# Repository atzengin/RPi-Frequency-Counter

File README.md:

# 2/4 channel frequency counter for RPi

Provides 2 32 bits or 4 16 bits independent counters on board.
For the UI software see [this page](https://github.com/atzengin/RPi-Frequency-Counter-Software)

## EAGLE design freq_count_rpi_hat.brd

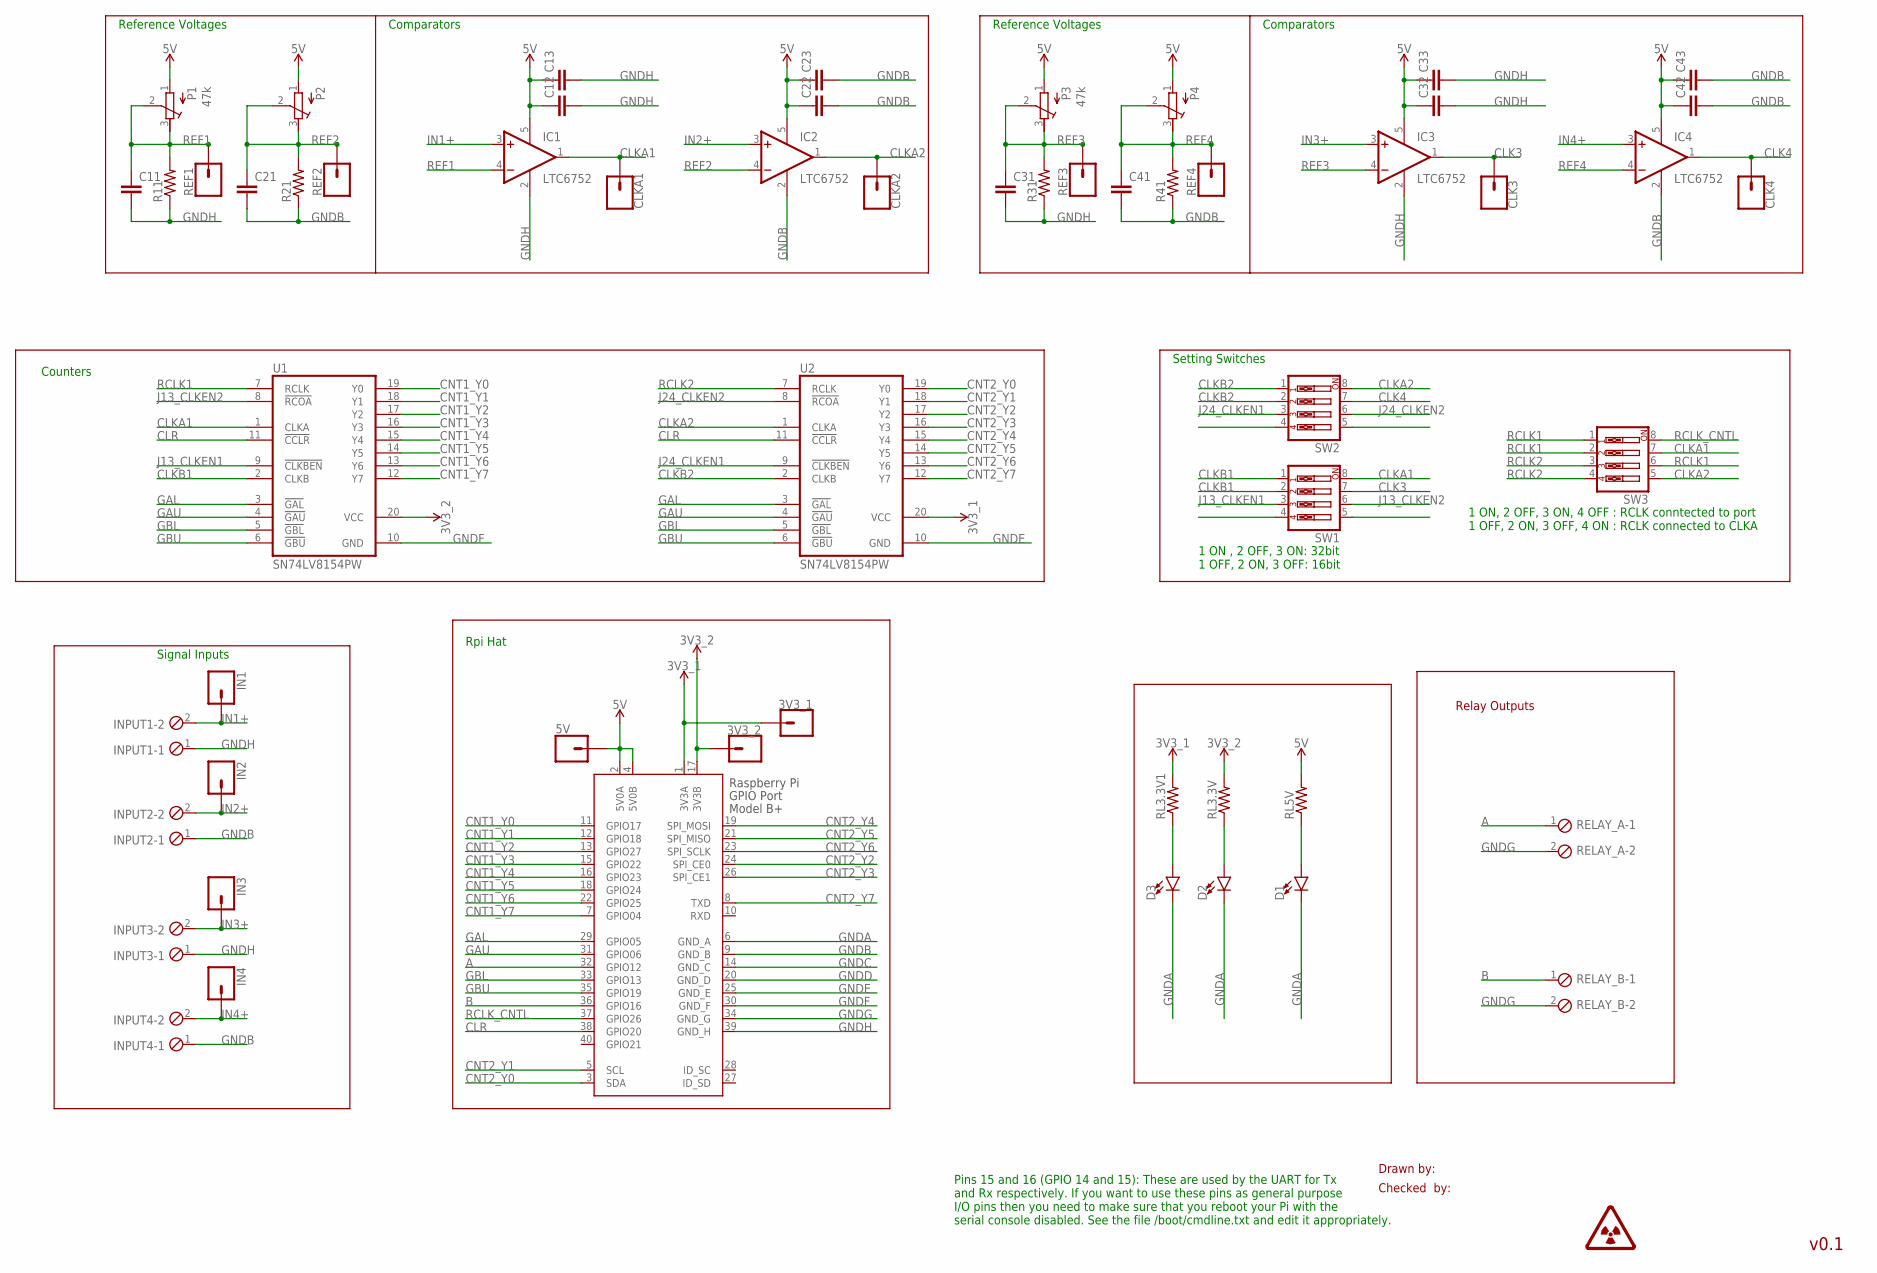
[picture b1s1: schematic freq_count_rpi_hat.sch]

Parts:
3V3_1, 3V3_2, 5V: CONN_01; 1X01
C11, C12, C13, C21, C22, C23, C31, C32, C33, C41, C42, C43: C-EUC1206; C1206
CLK3, CLK4: CONN_01; 1X01
CLKA1, CLKA2: CONN_01; 1X01
D1, D2, D3: LED1206; LED-1206
IC1, IC2, IC3, IC4: LTC6752; SOT23-5
IN1, IN2, IN3, IN4: CONN_01; 1X01
INPUT1, INPUT2, INPUT3, INPUT4: MPT2; 2POL254
P1, P3: 47k; RTRIM3296W
P2, P4: R-TRIMM3296W; RTRIM3296W
R11, R21, R31, R41: R-US_R1206; R1206
REF1, REF2, REF3, REF4: CONN_01; 1X01
RELAY_A: MPT2; 2POL254
RELAY_B: MPT2; 2POL254
RL3.3V, RL3.3V1, RL5V: R-US_R1206; R1206
SW1, SW2, SW3: SW_DIP-4; EDG-04
U1, U2: SN74LV8154PW; TSSOP20
X1: RASPI_BOARD_B+#_H; RASPI_BOARD_B+HAT

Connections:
5V: 5V.1, C12.1, C13.1, C22.1, C23.1, C32.1, C33.1, C42.1, C43.1, IC1.5 (V+), IC2.5 (V+), IC3.5 (V+), IC4.5 (V+), P1.1 (A), P2.1 (A), P3.1 (A), P4.1 (A), RL5V.2, X1.2 (5V0A), X1.4 (5V0B)
A: RELAY_A.1, X1.32 (GPIO12)
B: RELAY_B.1, X1.36 (GPIO16)
CLK3: CLK3.1, IC3.1 (OUT), SW1.7
CLK4: CLK4.1, IC4.1 (OUT), SW2.7
CLKA1: CLKA1.1, IC1.1 (OUT), SW1.8, SW3.7, U1.1 (CLKA)
CLKA2: CLKA2.1, IC2.1 (OUT), SW2.8, SW3.5, U2.1 (CLKA)
CLKB1: SW1.1, SW1.2, U1.2 (CLKB)
CLKB2: SW2.1, SW2.2, U2.2 (CLKB)
CLR: U1.11 (!CCLR!), U2.11 (!CCLR!), X1.38 (GPIO20)
CNT1_Y0: U1.19 (Y0), X1.11 (GPIO17)
CNT1_Y1: U1.18 (Y1), X1.12 (GPIO18)
CNT1_Y2: U1.17 (Y2), X1.13 (GPIO27)
CNT1_Y3: U1.16 (Y3), X1.15 (GPIO22)
CNT1_Y4: U1.15 (Y4), X1.16 (GPIO23)
CNT1_Y5: U1.14 (Y5), X1.18 (GPIO24)
CNT1_Y6: U1.13 (Y6), X1.22 (GPIO25)
CNT1_Y7: U1.12 (Y7), X1.7 (GPIO04)
CNT2_Y0: U2.19 (Y0), X1.3 (SDA)
CNT2_Y1: U2.18 (Y1), X1.5 (SCL)
CNT2_Y2: U2.17 (Y2), X1.24 (SPI_CE0)
CNT2_Y3: U2.16 (Y3), X1.26 (SPI_CE1)
CNT2_Y4: U2.15 (Y4), X1.19 (SPI_MOSI)
CNT2_Y5: U2.14 (Y5), X1.21 (SPI_MISO)
CNT2_Y6: U2.13 (Y6), X1.23 (SPI_SCLK)
CNT2_Y7: U2.12 (Y7), X1.8 (TXD)
GAL: U1.3 (!GAL!), U2.3 (!GAL!), X1.29 (GPIO05)
GAU: U1.4 (!GAU!), U2.4 (!GAU!), X1.31 (GPIO06)
GBL: U1.5 (!GBL!), U2.5 (!GBL!), X1.33 (GPIO13)
GBU: U1.6 (!GBU!), U2.6 (!GBU!), X1.35 (GPIO19)
GNDA: D1.C, D2.C, D3.C, X1.6 (GND_A)
GNDB: C21.2, C22.2, C23.2, C41.2, C42.2, C43.2, IC2.2 (V-), IC4.2 (V-), INPUT2.1, INPUT4.1, R21.1, R41.1, X1.9 (GND_B)
GNDC: X1.14 (GND_C)
GNDD: X1.20 (GND_D)
GNDE: U2.10 (GND), X1.25 (GND_E)
GNDF: U1.10 (GND), X1.30 (GND_F)
GNDG: RELAY_A.2, RELAY_B.2, X1.34 (GND_G)
GNDH: C11.2, C12.2, C13.2, C31.2, C32.2, C33.2, IC1.2 (V-), IC3.2 (V-), INPUT1.1, INPUT3.1, R11.1, R31.1, X1.39 (GND_H)
IN1+: IC1.3 (+IN), IN1.1, INPUT1.2
IN2+: IC2.3 (+IN), IN2.1, INPUT2.2
IN3+: IC3.3 (+IN), IN3.1, INPUT3.2
IN4+: IC4.3 (+IN), IN4.1, INPUT4.2
J13_CLKEN1: SW1.3, U1.9 (!CLKBEN!)
J13_CLKEN2: SW1.6, U1.8 (!RCOA!)
J24_CLKEN1: SW2.3, U2.9 (!CLKBEN!)
J24_CLKEN2: SW2.6, U2.8 (!RCOA!)
unnamed: D1.A, RL5V.1
unnamed: D2.A, RL3.3V.1
unnamed: D3.A, RL3.3V1.1
RCLK1: SW3.1, SW3.2, SW3.6, U1.7 (RCLK)
RCLK2: SW3.3, SW3.4, U2.7 (RCLK)
RCLK_CNTL: SW3.8, X1.37 (GPIO26)
REF1: C11.1, IC1.4 (-IN), P1.2 (S), P1.3 (E), R11.2, REF1.1
REF2: C21.1, IC2.4 (-IN), P2.2 (S), P2.3 (E), R21.2, REF2.1
REF3: C31.1, IC3.4 (-IN), P3.2 (S), P3.3 (E), R31.2, REF3.1
REF4: C41.1, IC4.4 (-IN), P4.2 (S), P4.3 (E), R41.2, REF4.1
VCC_1: 3V3_1.1, RL3.3V1.2, U2.20 (VCC), X1.1 (3V3A)
VCC_2: 3V3_2.1, RL3.3V.2, U1.20 (VCC), X1.17 (3V3B)

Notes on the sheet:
Drawn by:
Checked by:
v0.1
Pins 15 and 16 (GPIO 14 and 15): These are used by the UART for Tx and Rx respectively. If you want to use these pins as general purpose I/O pins then you need to make sure that you reboot your Pi with the serial console disabled. See the file /boot/cmdline.txt and edit it appropriately.
Signal Inputs
Reference Voltages
Comparators
Counters
Rpi Hat
Relay Outputs
1 ON , 2 OFF, 3 ON: 32bit 1 OFF, 2 ON, 3 OFF: 16bit
Setting Switches
1 ON, 2 OFF, 3 ON, 4 OFF : RCLK conntected to port 1 OFF, 2 ON, 3 OFF, 4 ON : RCLK connected to CLKA

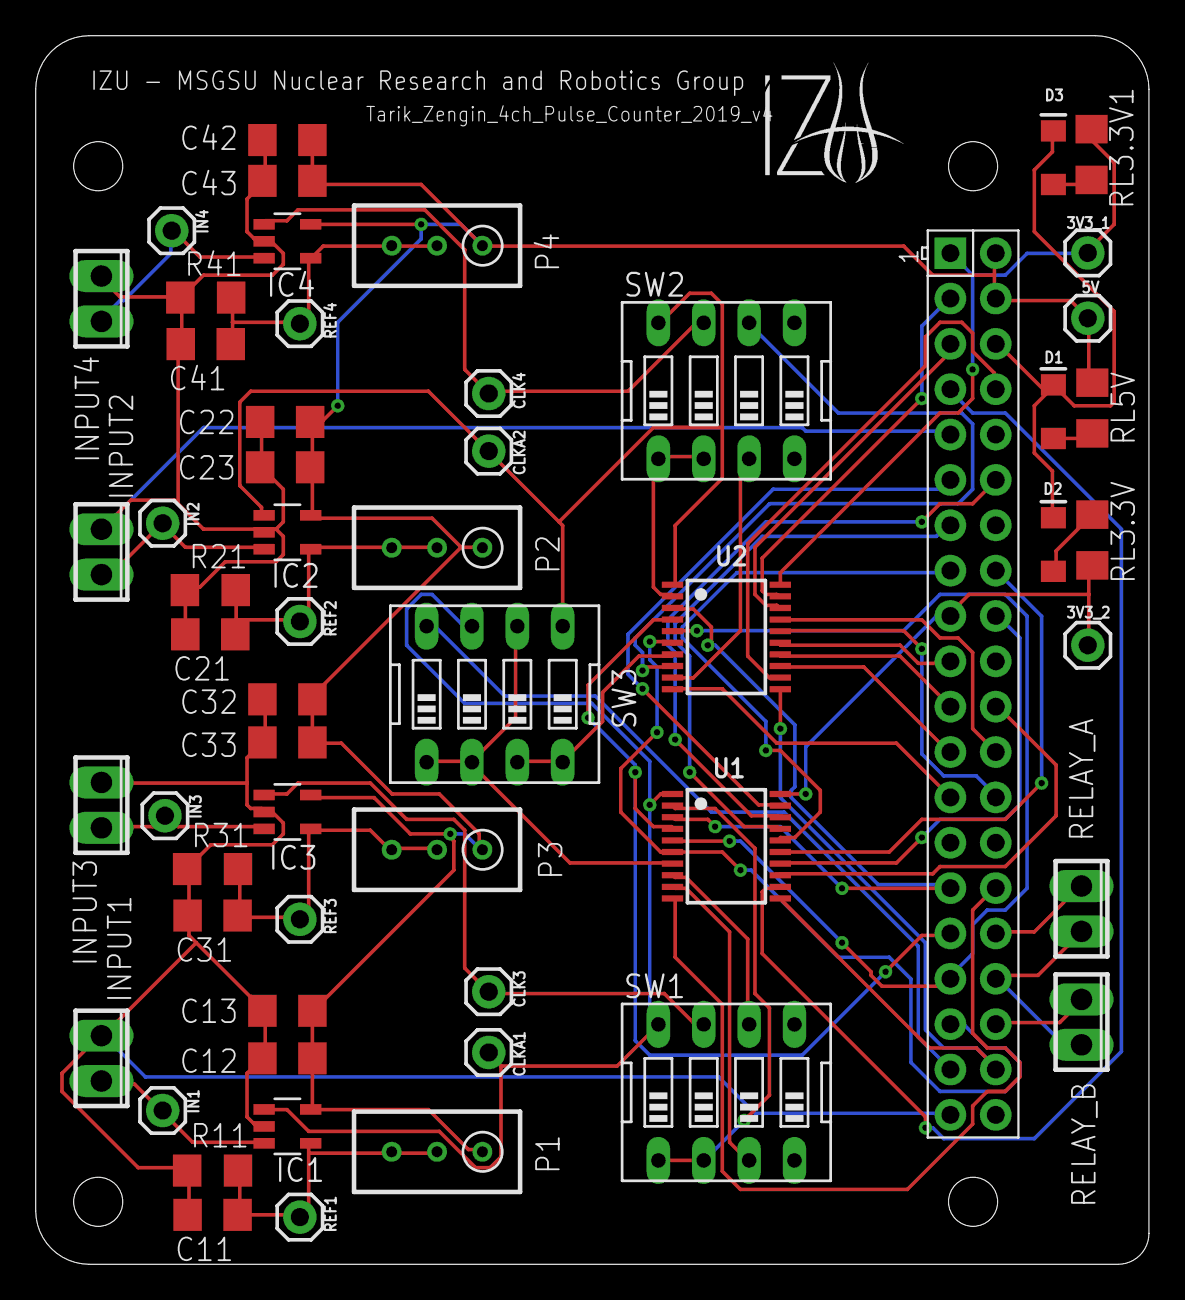
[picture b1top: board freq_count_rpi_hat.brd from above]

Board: 2 copper layers, 62.3 x 68.8 mm, 57 parts (0 on the bottom side), 56 nets.

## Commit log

2019-12-28 Updated with mode selection switches and mistakes in design were corrected

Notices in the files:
parts and their libraries:
74LV: Copyright (C) 2008, Bob Starr
SparkFun-Connectors: Licensing: Creative Commons ShareAlike 4.0 International - https://creativecommons.org/licenses/by-sa/4.0
